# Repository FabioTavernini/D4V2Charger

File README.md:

# D4v2Charger

A work-in-progress proof of concept for adding built-in USB-C charging to the
[Emisar D4v2](https://intl-outdoor.com/emisar-d4v2-high-power-led-flashlight.html) flashlight, using a
pogo-pin connector in place of removing the cell to charge it externally.

The charger PCB is a disc that sits sandwiched between the flashlight body
tube and the head, in the same joint where they normally screw together. A
spring contact on the board presses against the cell's positive terminal,
while the pogo-pin connector protrudes to the side to bring in USB-C power
through the body wall.

*Cutaway render: cell (green) above, charger PCB sandwiched at the
body/head joint below, with the spring contact touching the cell's positive
terminal and the pogo-pin connector (black) sticking out to the side.*

*Screenshot of Schematic (May be out of date lol)*

## Status

Early prototype / proof of concept. Nothing here has been validated in a
final build yet — expect rough edges, and treat all files as subject to
change.

## How it works

- A small ring-shaped PCB is sandwiched between the flashlight body and
  head, and charges the cell via a
  [TI BQ25185](https://www.ti.com/product/BQ25185) single-cell Li-ion linear
  charger (with integrated power path).
- A spring contact on the board makes the positive connection to the cell,
  so no wiring or modification of the cell itself is needed.
- Power comes in through a pair of spring-loaded pogo pins rather than a
  connector mounted directly on the PCB, so no permanent cutout is needed
  for a USB-C receptacle on the board itself.
- A custom pogo-pin connector part and a modified flashlight body/case were
  designed to accommodate the charging contacts and let the PCB sandwich
  fit at the body/head joint.

## Repo contents

- `pcb/` — KiCad project for the charger board
  - `D4v2Charger.kicad_pro` / `.kicad_sch` / `.kicad_pcb` — schematic and PCB layout
  - `D4v2Charger.step` — 3D export of the finished board
  - `PogoPinConnector/` — FreeCAD model and STEP export of the pogo-pin connector
  - `D4v2Charger-backups/` — automatic KiCad backups (safe to ignore)
- `case/` — FreeCAD model of the modified flashlight body/case to fit the
  charging hardware

## Tools used

- [KiCad](https://www.kicad.org/) for schematic capture and PCB layout
- [FreeCAD](https://www.freecad.org/) for mechanical/case design

## Disclaimer

This is a hobbyist mod to a battery-powered lighting device. Modifying
charging circuitry and battery contacts carries fire/safety risk if done
incorrectly. Use at your own risk.

## License

Licensed under the [CERN Open Hardware Licence Version 2 - Strongly
Reciprocal](LICENSE) (CERN-OHL-S-2.0).

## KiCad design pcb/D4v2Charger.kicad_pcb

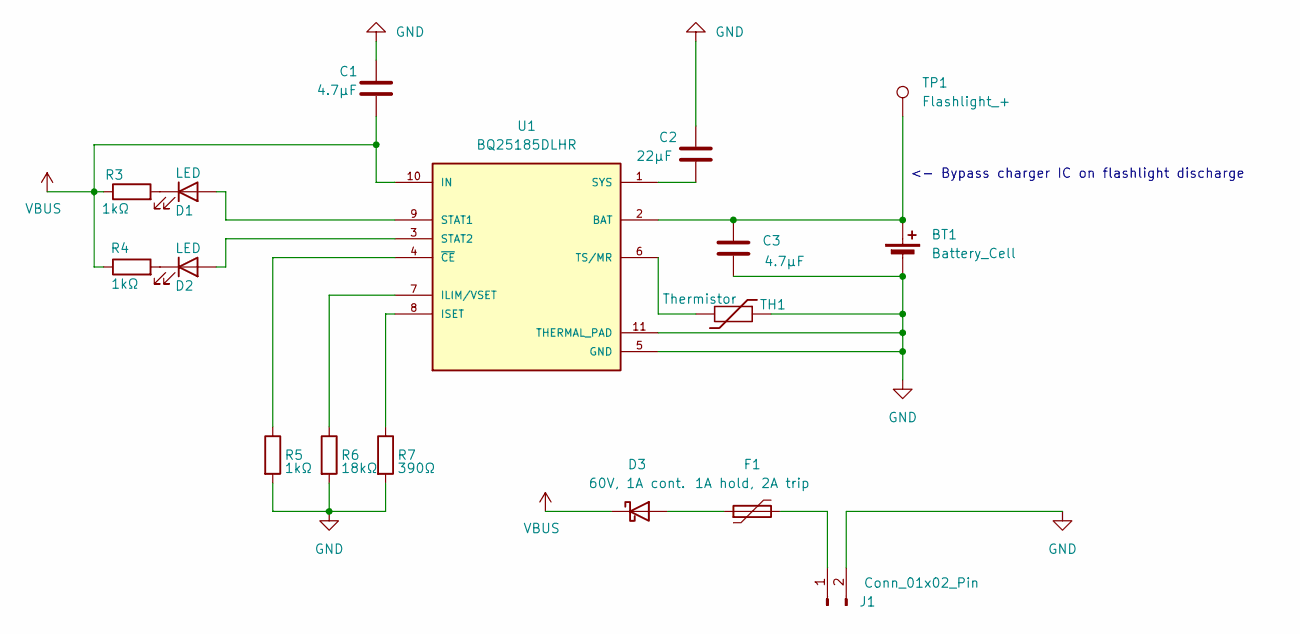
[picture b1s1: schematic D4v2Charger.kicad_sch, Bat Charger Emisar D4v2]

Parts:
BT1: Battery_Cell
C1, C3: 4.7µF; C_0402_1005Metric
C2: 22µF; C_0402_1005Metric
D1, D2: LED; LED_0603_1608Metric
D3: 60V, 1A cont.; DIO_PMEG6010CEJF
F1: 1A hold, 2A trip; 0402L100SLKR
J1: Conn_01x02_Pin; PinHeader_1x02_P2.54mm_Vertical
R3, R4, R5: 1kΩ; R_0402_1005Metric
R6: 18kΩ; R_0402_1005Metric
R7: 390Ω; R_0402_1005Metric
TH1: Thermistor; THERM_NTCG103JF103FT1
TP1: Flashlight_+; TestPoint_Pad_D6.0mm_spring
U1: BQ25185DLHR; Texas_DLH0010A_WSON-10-1EP_2.2x2mm_P0.4mm_EP0.9x1.5mm; PARTREV OCTOBER 2023

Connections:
GND: BT1.2 (-), C1.1, C2.1, C3.2, J1.2, R5.2, R6.2, R7.2, TH1.1, U1.5 (GND), U1.11 (THERMAL_PAD)
unnamed: BT1.1 (+), C3.1, TP1.1, U1.2 (BAT)
unnamed: D1.2 (A), U1.9 (STAT1)
unnamed: D1.1 (K), R3.2
unnamed: D2.2 (A), U1.3 (STAT2)
unnamed: D2.1 (K), R4.2
unnamed: D3.2 (A), F1.1
unnamed: F1.2, J1.1
unnamed: R6.1, U1.7 (ILIM/VSET)
unnamed: R7.1, U1.8 (ISET)
unnamed: C2.2, U1.1 (SYS)
unnamed: TH1.2, U1.6 (TS/MR)
unnamed: R5.1, U1.4 (~CE)
VBUS: C1.2, D3.1 (K), R3.1, R4.1, U1.10 (IN)

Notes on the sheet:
<- Bypass charger IC on flashlight discharge

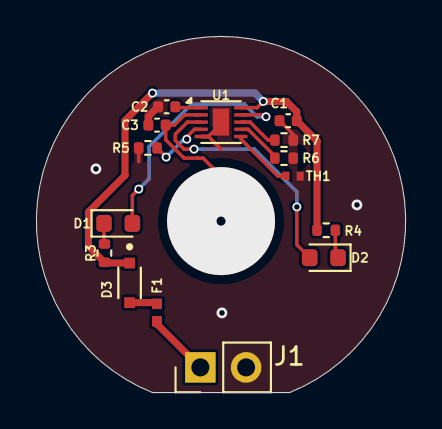
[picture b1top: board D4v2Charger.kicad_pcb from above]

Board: 2 copper layers, 20.5 x 19.8 mm, 16 parts (0 on the bottom side), 14 nets.

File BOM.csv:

"Id";"Designator";"Footprint";"Quantity";"Designation";"Supplier and ref";comment;Link;price
1;"TP1";"TestPoint_Pad_D6.0mm_spring";1;"Flashlight_+";;Spring, 6mm diameter 25° banking if available, for + terminal;https://de.aliexpress.com/item/1005005667884016.html?spm=a2g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;
2;"U1";"Texas_DLH0010A_WSON-10-1EP_2.2x2mm_P0.4mm_EP0.9x1.5mm";1;"BQ25185DLHR";;digikey, pretty expensive;https://www.digikey.com/en/products/detail/texas-instruments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;2.28
3;"D3";"DIO_PMEG6010CEJF";1;"60V, 1A cont.";;not available, see alternatives;https://de.aliexpress.com/item/1005012406460192.html?spm=a2g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;
4;"D1,D2";"LED_0603_1608Metric";2;"LED";;1000pcs reel;https://de.aliexpress.com/item/1005009084941790.html?spm=a2g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;4.25
5;"C2";"C_0402_1005Metric";1;"22µF";;50pcs;https://de.aliexpress.com/item/1005005108653334.html?spm=a2g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;3.47
6;"C1,C3";"C_0402_1005Metric";2;"4.7µF";;6.3v 50pcs;https://de.aliexpress.com/item/1005012364450156.html?spm=a2g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;1.31
7;"R4,R5,R3";"R_0402_1005Metric";3;"1kΩ";;100pcs;https://de.aliexpress.com/item/1005008851185252.html?spm=a2g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;0.21
8;"R6";"R_0402_1005Metric";1;"18kΩ";;;https://de.aliexpress.com/item/1005008851185252.html?spm=a2g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;0.21
9;"R7";"R_0402_1005Metric";1;"390Ω";;;https://de.aliexpress.com/item/1005008851185252.html?spm=a2g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;0.21
10;"F1";"0402L100SLKR";1;"1A hold, 2A trip";;digikey, pretty expensive;https://www.digikey.com/en/products/detail/littelfuse-inc/04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;3.28
11;"J1";"PinHeader_1x02_P2.54mm_Vertical";1;"Conn_01x02_Pin";;5pcs;https://de.aliexpress.com/item/1005006531774076.html?spm=a2g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;10.39
12;"TH1";"THERM_NTCG103JF103FT1";1;"Thermistor";;TDK NTCG103JF103FT1, 10kΩ NTC 0402;;

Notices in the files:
pcb/D4v2Charger.kicad_sch:
Copyright (c) 2026 Fabio Tavernini
